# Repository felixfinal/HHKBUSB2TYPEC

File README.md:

# HHKBUSB2TYPEC

Change HHKB Pro2 USB from MINI-B to TPYE C

1. I confirm that the USB Mini-B model used on the HHKB is HRS UX60-MB-5S8
2. I would like to use Molex 2171790001 as a replacement for the original USB, while minimizing any damage to the existing structure
~~3. Using a PCB thickness of 1.2mm, there may be a 0.2mm gap that needs to be adjusted using tape~~
3. sing a PCB thickness of 1.2mm is a bit thick. It is possible to use a PCB with a thickness of 1.0mm
4. To save costs, we need to use PCB with a regular process and modify the half-hole boards with sandpaper

The current project is in testing phase, and I have already produced the PCB and purchased the materials.

***

## Raw Materials

## Adjust PCB

use sandpaper to adjust the PCB

## Soldering

## Assembly

Use sandpaper to enlarge the outer shell holes slightly and proceed with the assembly.

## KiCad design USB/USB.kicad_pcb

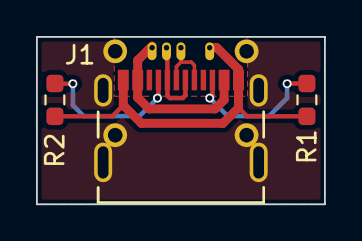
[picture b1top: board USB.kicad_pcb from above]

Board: 2 copper layers, 16.0 x 9.3 mm, 3 parts (0 on the bottom side), 7 nets.

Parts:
J1: 2171790001; 2171790001_MOL
R1, R2: 5K1; R_0603_1608Metric_Pad0.98x0.95mm_HandSolder

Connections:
+5V: J1.A4/B9 (VBUS), J1.B4/A9 (VBUS)
/DN: J1.A7 (DN1), J1.B7 (DN2)
/DP: J1.A6 (DP1), J1.B6 (DP2)
GND: J1.A1/B12 (GND), J1.B1/A12 (GND), R1.1, R2.1
GNDPWR: J1.13 (Shell1), J1.14 (Shell2), J1.15 (Shell3), J1.16 (Shell4)
unnamed: J1.A5 (CC1), R2.2
unnamed: J1.B5 (CC2), R1.2

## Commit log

2023-07-03 Not test
2023-07-07 Add img change test ok
